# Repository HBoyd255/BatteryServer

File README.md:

# Battery Server

A Google App scripts based project to monitor and display the current battery
percentages of my various smart devices.

This project contains 3 main sections;

1. Device Client (Uploader): This client-side application runs on each
   individual device, monitoring the battery level and regularly uploading this
   data to the server.

2. Server Application: This is the heart of the system that receives and
   processes battery level data sent from each device. It organizes and stores 
   the information for retrieval.

3. User Client (Downloader): This application retrieves the battery levels for 
each device from the server, providing a comprehensive view of all monitored 
devices.

## Contents

- [Getting Started](GettingStarted/)
  - [iOS Client](GettingStarted/iosClient/README.md)
  - [iOS Client](GettingStarted/iosClient/README.md)
- [Libraries used](#Libraries-used)

## Libraries used

- KiCad
  - [heltec_htit-wb32](https://github.com/bartloeff/heltec_htit-wb32)
  - [Heltec WiFi LoRa 32 Shield](https://grabcad.com/library/heltec-wifi-lora-32-shield-1)
  - [Switch Push Button](https://www.snapeda.com/parts/1825910-6/TE%20Connectivity/view-part/?ref=search&t=momentary%20switch)
  - [Red 617nm LED Indication](https://www.snapeda.com/parts/WP7113ID/Kingbright/view-part/?ref=search&t=led)
- Ardiuno
  - [ArduinoJson 6.21.3](arduinojson.org)
  - [Heltec ESP32 Dev-Boards 1.1.1](http://heltec.cn)
- Python
  - [psutil 5.9.4](https://github.com/giampaolo/psutil)
  - [Requests 2.31.0](https://requests.readthedocs.io/en/latest/)

## TO-DO

- [ ] Write a quick-start for the App scripts Server.
- [ ] Write a quick-start for the Python Client.
- [ ] Set the Favicon for the HTML page.
- [ ] Rewrite README.md.
- [ ] fix the downloader code by adding defensive copying to the retrieveData()
      function.

### Possible future features

- Add the ability to upload the "is_charging" status.
- Add more ways to display the information from the server.

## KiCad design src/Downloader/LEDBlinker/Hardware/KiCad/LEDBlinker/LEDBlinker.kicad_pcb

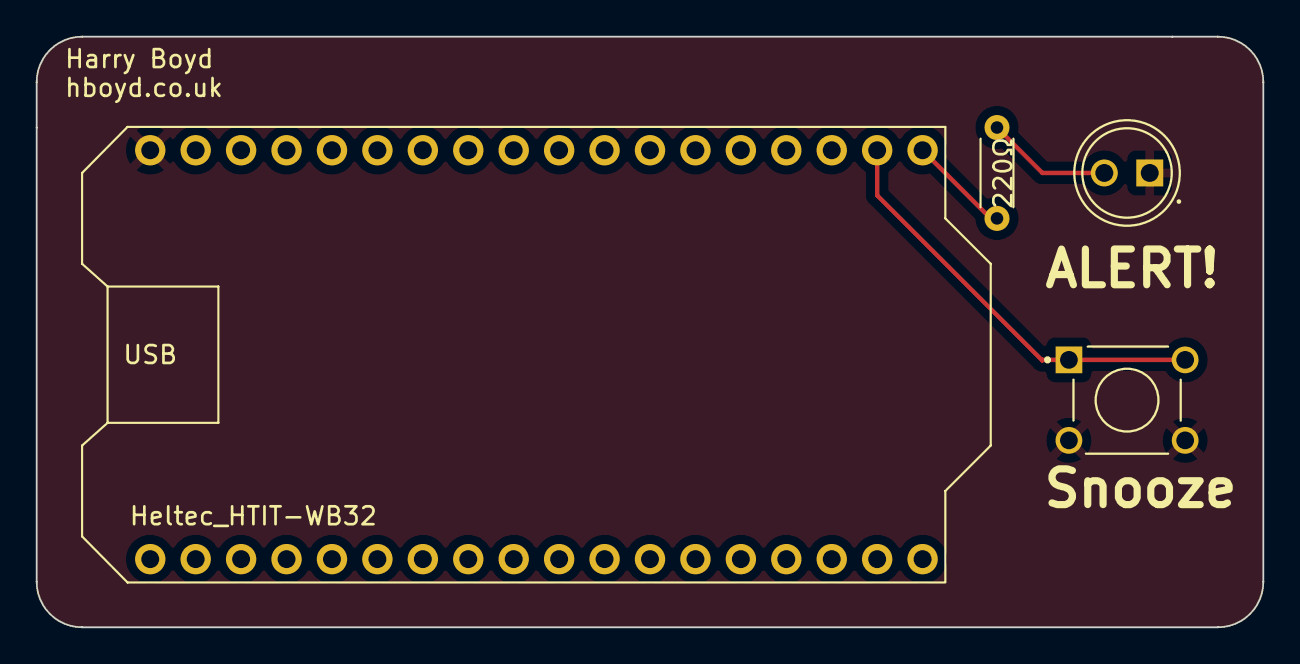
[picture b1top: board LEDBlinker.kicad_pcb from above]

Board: 2 copper layers, 68.6 x 33.0 mm, 4 parts (0 on the bottom side), 4 nets.

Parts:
D1: WP7113ID; LED_WP7113ID
R1: 220; R_Axial_DIN0204_L3.6mm_D1.6mm_P5.08mm_Horizontal
SW1: 1825910-6; SW_1825910-6-4
U1: Heltec_HTIT-WB32

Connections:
GND: D1.C, SW1.3, SW1.4, U1.28 (GND)
unnamed: D1.A, R1.1
unnamed: R1.2, U1.21
unnamed: SW1.1, SW1.2, U1.22

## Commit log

2023-08-01 removed Unneeded Functions
2023-08-01 doPost adds value to table
2023-08-01 Imported existing python code
2023-08-01 updated uploader code to send data as JSON
2023-08-02 HTTP get working
2023-08-02 Refactored App Scripts
2023-08-02 updated TODO list
2023-08-03 Separated Json Control into its own file
2023-08-03 Basic HTML page now working
2023-08-05 created HTML page
2023-08-08 Added PSEUDO_BATTERY Debug flag
2023-08-08 changed some starting values
2023-08-09 Designed PCB for LEDBlinker
2023-09-08 Finished LEDBlinker
2023-09-08 restructured Repo
2023-11-01 Updated silkscreen
2023-12-07 started separating out constant values
2023-12-07 Updated Reference to Battery Server in README
2023-12-07 Moved
2023-12-07 Created Template Secret Data
2023-12-07 Mopped up the mess I just made
2024-04-01 replaced url_manager with cooking-with-gas
2024-11-11 Reformatted code
